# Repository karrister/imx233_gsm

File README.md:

IMX233 GSM
=============

This project started as my thesis project for the University (of applied sciences) of Helsinki. The project is about making a simple open source, Linux based cellular phone. In the heart of the device are an Olimex made Olinuxino (the original) IMX233 development board, connected over an application UART to a SIM900 GPRS GSM-development board. I will also connect a self-made keypad (1 button at first stage) and a self-made screen (1 LED indicator at first stage).

For now I have seized the PCB design for a board combining the two Chips on a shared board, as the final design did not meet the requirements for printing. I will publish the current PCB design files (kicad) here and also plan to continue the work to have a printed board eventually.

Currently I have created a 4.1.1 kernel, running with Debian Jessie on the CPU. The Software for interfacing the Hardware will be a set of Python scripts, communicating with the Chip, parsing the AT commands as well as controlling the custom keypad and screen.

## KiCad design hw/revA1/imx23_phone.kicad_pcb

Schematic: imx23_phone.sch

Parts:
C1, C3: 10uF/6.3V
C2, C4, C5, C6, C7, C8, C9, C10, C12, C24, C29, C31, C33, C34, C46, C48, C49: 100nF
C11, C20, C23, C26, C28, C30, C32, C35, C36, C42, C43, C44, C45, C47, C50, C51, C54, C55: 22uF/6.3V
C13: 470uF
C14, C16, C17, C19, C25: 33pF
C15, C22: 10pF
C18: 4.7uF
C21: NC(10pF)
C27, C39: 1uF
C37, C38: 15pF
C40, C41: NC
C52, C53: 220uF/10V/105C
D1, D5: DIODESCH
D2: BAT54C
D3: LED
D4: AVALANCHE-SMBJ6.0A
J1: AUDIO_3.5
J2, J3: U.FL
J4: MICROSD_SIM_COMBO
J5: USB_MINI
L1: 22uH/1.5A/YS75/7x8mm
L2: FB0805/600R/2A
L3: 470nH/0805/1.76R/250mA
L4: FB0805/600R/200mA
P1: BATT
P2: EXT_GSM_POWER
P3: MIC_P
P4: MIC_N
P5: SPK_P
P6: SPK_GND
P7: RTC_VDD
P8: RTC_GND
P9: GSM_PWR
P10: SPK_N
P11: GSM_DBG_RX
P12: GSM_DBG_TX
P13: STATUS
P14: NETLIGHT
P15: CONN_4
P16: SIM_VPP
P17: LCD_D11
P18: I2C
P19: LCD_CS
P20: 5V_OUT
P21: GPIO4/LRADC0
P22: GPIO2
P23: GPIO3
P24: GPIO1
R1, R12, R14: 120
R2, R3, R23, R26: 1k/1%
R4: NC(0)
R5, R36: 0
R6, R7, R9, R10, R27, R29, R34: 10k
R8: 68
R11: 1k
R13, R15, R24, R43, R44, R45, R46: 4k7
R16: 10
R17, R35, R39, R42: 47k
R18: 0R
R19, R20, R21: 22
R22, R30, R31, R32: 100k
R25, R37, R38: 2k2
R28: 1M
R33: NA(47k)
R40, R41: NC(47k)
SW1: POWER
SW2: REC
T1: PMGD175XN
T2: BSV52
U1: FREESCALE-IMX233
U2: HY5DU121622D
U3: SMA_JACK
U4: SIM900
U5: LCD_NOKIA5110
X1: Q24.000MHz/HC-49SM/SMD/20ppm/20pF

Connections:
+2.5V: C1.1, C2.1, C3.1, C4.1, C5.1, C6.1, C7.1, C8.1, C9.1, C42.1, C44.1, C46.1, C48.1, R2.1, R27.1, U1.38 (VDDIO_EMIQ), U1.45 (VDDIO_EMI1), U1.53 (VDDIO_EMI2), U1.106 (VDDM/LRADC4), U2.1 (VDD1), U2.3 (VDDQ1), U2.9 (VDDQ2), U2.15 (VDDQ3), U2.18 (VDD2), U2.33 (VDD3), U2.55 (VDDQ4), U2.61 (VDDQ5)
+3.3V: C26.1, C28.1, C29.1, C43.1, C45.1, L3.2, P18.1, R24.2, R29.2, R30.2, R31.2, R32.2, R34.1, R35.2, R37.1, R38.1, R43.2, R44.2, R45.2, R46.2, U1.18 (VDDIO33_1), U1.92 (VDDIO33_3), U1.95 (DCDC_VDDIO), U5.6 (VCC)
+5V: C32.1, C34.1, C50.1, C51.1, L2.1, P20.1, U1.102 (VDD5V)
GND: C1.2, C2.2, C3.2, C4.2, C5.2, C6.2, C7.2, C8.2, C10.2, C11.2, C12.2, C13.2, C14.2, C15.2, C16.2, C17.2, C18.2, C19.2, C20.2, C21.2, C22.2, C23.2, C24.2, C25.2, C26.2, C28.2, C29.2, C30.2, C31.2, C32.2, C33.2, C34.2, C35.2, C36.2, C37.2, C38.2, C39.2, C40.2, C41.2, C42.2, C43.2, C44.2, C45.2, C46.2, C47.2, C48.2, C49.2, C50.2, C51.2, C52.2, C53.2, C54.2, C55.2, D4.1 (A), J2.2 (GND), J2.3 (GND), J3.2 (GND), J3.3 (GND), J4.G1 (GND), J4.G2 (GND), J4.G3 (GND), J4.S4 (GND), J4.T6 (VSS), J5.5 (GND), L4.1, P1.2 (PM), P4.1, P6.1, P8.1, P15.3, P18.4, R3.2, R17.2, R22.1, R25.1, R28.2, R33.1, R39.1, R40.1, R41.1, R42.1, T2.2 (E), U1.30 (VSSD1), U1.35 (VSSD2), U1.98 (DCDC_GND), U1.105 (VSSA4), U1.112 (VSSA1), U1.118 (VSSA2), U2.6 (VSSQ1), U2.12 (VSSQ2), U2.34 (VSS1), U2.48 (VSS2), U2.52 (VSSQ3), U2.58 (VSSQ4), U2.64 (VSSQ5), U2.66 (VSS3), U3.2 (GND), U3.3 (GND), U3.4 (GND), U3.5 (GND), U4.17 (GND), U4.18 (GND), U4.20 (MIC_N), U4.29 (GND), U4.39 (GND), U4.45 (GND), U4.46 (GND), U4.53 (GND), U4.54 (GND), U4.58 (GND), U4.59 (GND), U4.61 (GND), U4.62 (GND), U4.63 (GND), U4.64 (GND), U4.65 (GND), U5.8 (GND)
unnamed: R11.2, U4.1 (PWRKEY)
unnamed: P9.1, R11.1, T2.3 (C)
unnamed: R15.2, R17.1, T2.1 (B)
unnamed: R13.2, U4.4 (RI)
unnamed: P14.1, U4.52 (NETLIGHT)
unnamed: P13.1, U4.66 (STATUS)
unnamed: C41.1, J3.1 (SIG), R18.2
unnamed: C40.1, R18.1, U4.60 (RF_ANT)
unnamed: J2.1 (SIG), U3.1 (RF)
unnamed: C18.1, P7.1, U4.26 (VRTC)
unnamed: C35.1, C36.1, D1.2 (K), U1.101 (VDD4P2)
unnamed: R15.1, U1.82 (GPMI_CE0N)
unnamed: R13.1, U1.81 (GPMI_CE1N)
unnamed: J1.2 (L), R14.2, U1.113 (HPL)
unnamed: J1.3 (R), R12.2, U1.109 (HPR)
unnamed: J1.1 (GND), R12.1, R14.1, U1.111 (HP_VGND)
unnamed: P2.1, R4.1
unnamed: J4.T8 (DAT1), R30.1, U1.85 (SSP1_DATA1/I2C_SCL/JTAG_TCLK)
unnamed: J4.S6 (I/O), R21.2
unnamed: P12.1, U4.27 (DEBUG_TXD)
unnamed: P11.1, U4.28 (DEBUG_RXD)
unnamed: J4.S2 (RST), R19.2
unnamed: R20.1, U4.32 (SIM_CLK)
unnamed: J4.S3 (CLK), R20.2
unnamed: R21.1, U4.31 (SIM_DATA)
unnamed: J4.S1 (VCC), U4.30 (SIM_VDD)
unnamed: R35.1, U1.14 (LCD_RS)
unnamed: J4.T1 (DAT2), R32.1, U1.86 (SSP1_DATA2/I2C_SDA/JTAG_RTCK)
unnamed: J4.T7 (DAT0), R31.1, U1.84 (SSP1_DATA0/SPI1_MISO/JTAG_TDI)
unnamed: J4.T3 (CMD), R29.1, U1.83 (SSP1_CMD/SPI1_MOSI/JTAG_TDO)
unnamed: J4.T5 (CLK), U1.90 (SSP1_SCK/SPI1_SCK/JTAG_TRST)
unnamed: J4.T2 (CD/DAT3), R28.1, U1.87 (SSP1_DATA3/SPI1_SS#/JTAG_TMS)
unnamed: R7.2, T1.4 (S2), U4.10 (RXD)
unnamed: R9.2, T1.6 (D1), U1.128 (I2C_SDA/GPMI_CE2N/AUART1_RX)
unnamed: R6.1, T1.1 (S1), U4.9 (TXD)
unnamed: R10.2, T1.3 (D2), U1.127 (I2C_SCL/GPMI_RDY2/AUART1_TX)
unnamed: R6.2, R7.1, T1.2 (G1), T1.5 (G2), U4.15 (VDD_EXT)
unnamed: R19.1, U4.33 (SIM_RST)
unnamed: C27.1, U4.21 (SPK_P)
unnamed: C14.1, P3.1, R8.1
unnamed: C17.1, R8.2, U4.19 (MIC_P)
unnamed: R34.2, SW2.2
unnamed: R36.1, U1.27 (GPMI_D04/LCD_D12/SSP2_DATA4)
unnamed: D2.1 (Anode), U1.125 (PWM0/ROTARYA/DUART_RX)
unnamed: D2.3 (cathode), R24.1
unnamed: D2.2 (AK), P15.1
unnamed: R40.2, R44.1, U1.3 (LCD_D01)
unnamed: R33.2, U1.7 (LCD_D05)
unnamed: C33.1, SW1.2, U1.120 (VDDXTAL)
unnamed: R26.2, U1.119 (PSWITCH)
unnamed: R42.2, R46.1, U1.5 (LCD_D03)
unnamed: R41.2, R45.1, U1.4 (LCD_D02)
unnamed: R39.2, R43.1, U1.2 (LCD_D00)
unnamed: R22.2, R23.1, R26.1, R36.2, SW1.1, SW2.1
unnamed: C49.1, R23.2
unnamed: P22.1, U1.17 (LCD_DOTCK/GPMI_RDY3)
unnamed: J5.S (SHIELD), L4.2
unnamed: P21.1, U1.108 (LRADC0)
unnamed: P23.1, U1.20 (GPMI_ALE/LCD_D17)
unnamed: P24.1, U1.34 (GPMI_WPN)
unnamed: P10.1, U4.22 (SPK_N)
unnamed: P17.1, U1.25 (GPMI_D03/LCD_D11/SSP2_DATA3)
unnamed: R4.2, R5.1, U4.55 (VBAT), U4.56 (VBAT), U4.57 (VBAT)
unnamed: P19.1, U1.32 (GPMI_RDY0/SSP2_DETECT), U5.2 (CS)
unnamed: J4.S5 (VPP), P16.1
unnamed: C22.1, L1.1, U1.99 (DCDC_LP)
unnamed: C38.1, U1.121 (XTALO), X1.1
unnamed: D3.2 (K), R25.2
unnamed: D3.1 (A), U1.88 (SSP1_DETECT/GPMI_CE3N/USB_ID)
unnamed: P15.4, U1.89 (DEBUG)
unnamed: P15.2, U1.126 (PWM1/ROTARYB/DUART_TX)
unnamed: C21.1, L1.2, U1.97 (DCDC_LN1)
unnamed: C39.1, U1.117 (VAG)
unnamed: C20.1, C30.1, C31.1, C47.1, U1.1 (VDDD1), U1.93 (VDDD3), U1.94 (DCDC_VDDD)
unnamed: C23.1, C24.1, U1.96 (DCDC_VDDA), U1.110 (VDDA1)
unnamed: U1.9 (LCD_D07), U5.1 (RST)
unnamed: U1.8 (LCD_D06), U5.3 (DC)
unnamed: U1.91 (PWM2/GPMI_RDY3), U5.7 (LIGHT)
unnamed: U1.33 (GPMI_WRN/SSP2_SCK), U5.5 (CLK)
unnamed: U1.21 (GPMI_RDY1/SSP2_CMD), U5.4 (DIN)
unnamed: J5.3 (D+), U1.124 (USB_DP)
unnamed: D5.1 (A), J5.1 (VBUS)
unnamed: C52.1, C53.1, D4.2 (K), D5.2 (K), L2.2
unnamed: P18.3, R37.2, U1.15 (LCD_HSYNC/I2C_SDA)
unnamed: P18.2, R38.2, U1.11 (LCD_ENABLE/I2C_SCL)
unnamed: J5.2 (D-), U1.123 (USB_DM)
unnamed: C54.1, C55.1, J4.T4 (VDD), L3.1
unnamed: C9.2, C10.1, R2.2, R3.1, U2.49 (VREF)
unnamed: C15.1, C16.1, C19.1, P5.1, R16.1
unnamed: C25.1, C27.2, R16.2
unnamed: U1.72 (EMI_A04), U2.35 (A4)
unnamed: U1.51 (EMI_D08), U2.54 (DQ8)
unnamed: U1.78 (EMI_CKE), U2.44 (CKE)
unnamed: U1.60 (EMI_D14), U2.63 (DQ14)
unnamed: U1.62 (EMI_RASN), U2.23 (/RAS)
unnamed: U1.50 (EMI_D07), U2.13 (DQ7)
unnamed: U1.58 (EMI_D13), U2.62 (DQ13)
unnamed: U1.64 (EMI_A12), U2.42 (A12)
unnamed: U1.73 (EMI_A03), U2.32 (A3)
unnamed: U1.61 (EMI_CASN), U2.22 (/CAS)
unnamed: U1.40 (EMI_DQS1), U2.51 (UDQS)
unnamed: U1.54 (EMI_D10), U2.57 (DQ10)
unnamed: U1.55 (EMI_D11), U2.59 (DQ11)
unnamed: U1.68 (EMI_A08), U2.39 (A8)
unnamed: U1.76 (EMI_A00), U2.29 (A0)
unnamed: U1.69 (EMI_A07), U2.38 (A7)
unnamed: U1.66 (EMI_A10), U2.28 (A10/AP)
unnamed: U1.65 (EMI_A11), U2.41 (A11)
unnamed: U1.56 (EMI_DQM1), U2.47 (UDM)
unnamed: U1.70 (EMI_A06), U2.37 (A6)
unnamed: U1.80 (EMI_BA1), U2.27 (BA1)
unnamed: U1.52 (EMI_D09), U2.56 (DQ9)
unnamed: U1.71 (EMI_A05), U2.36 (A5)
unnamed: U1.59 (EMI_D15), U2.65 (DQ15)
unnamed: U1.74 (EMI_A02), U2.31 (A2)
unnamed: U1.77 (EMI_WEN), U2.21 (/WE)
unnamed: U1.49 (EMI_D06), U2.11 (DQ6)
unnamed: U1.57 (EMI_D12), U2.60 (DQ12)
unnamed: U1.67 (EMI_A09), U2.40 (A9)
unnamed: U1.75 (EMI_A01), U2.30 (A1)
unnamed: U1.46 (EMI_DQM0), U2.20 (LDM)
unnamed: U1.48 (EMI_D05), U2.10 (DQ5)
unnamed: U1.41 (EMI_D00), U2.2 (DQ0)
unnamed: U1.79 (EMI_BA0), U2.26 (BA0)
unnamed: R27.2, U1.63 (EMI_CE0N), U2.24 (/CS)
unnamed: R1.2, U1.37 (EMI_CLKN), U2.46 (/CK)
unnamed: R1.1, U1.36 (EMI_CLK), U2.45 (CK)
unnamed: U1.47 (EMI_D04), U2.8 (DQ4)
unnamed: U1.44 (EMI_D03), U2.7 (DQ3)
unnamed: U1.42 (EMI_D02), U2.5 (DQ2)
unnamed: U1.43 (EMI_D01), U2.4 (DQ1)
unnamed: U1.39 (EMI_DQS0), U2.16 (LDQS)
unnamed: C11.1, C12.1, C13.1, D1.1 (A), P1.1, R5.2, R9.1, R10.1, U1.100 (DCDC_BATTERY), U1.103 (BATT)
unnamed: C37.1, U1.122 (XTALI), X1.2

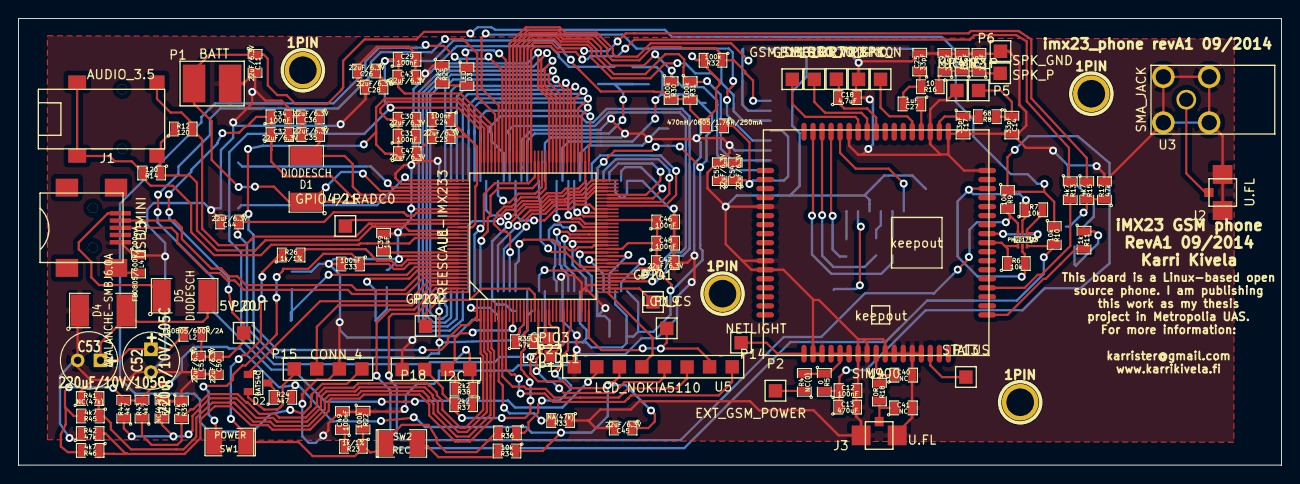
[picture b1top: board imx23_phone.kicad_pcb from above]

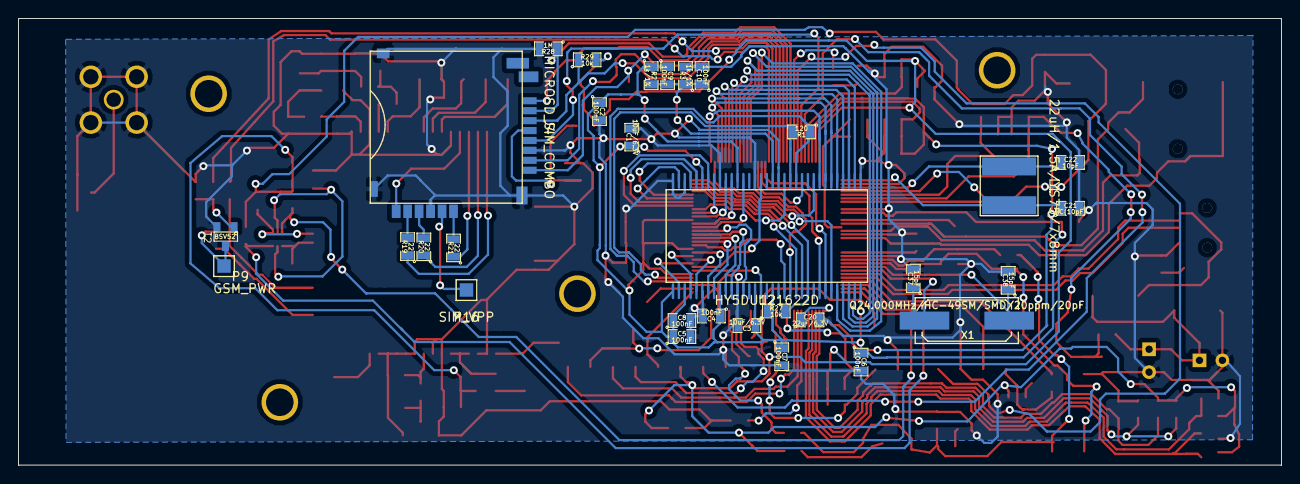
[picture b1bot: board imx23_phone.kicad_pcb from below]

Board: 2 copper layers, 140.0 x 49.5 mm, 153 parts (31 on the bottom side), 138 nets.

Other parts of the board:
1PIN, 1PIN#2, 1PIN#3, 1PIN#4: P***; 1pin

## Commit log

2016-03-19 :circus_tent: Added .gitattributes
2016-03-19 First commit *License and readme files *Basic Python infra stub files
2016-03-19 Infra skeleton *Introducing very basic main infra *Introducing basic classes and functions as stubs
2016-03-19 UART write stub *Bus driver write stub function
2016-08-29 Python framework works *Very basic python framework is now running
2016-09-17 SIM900 connection test *A connection test for SIM900 chip for testing connectivity with the Chip, as well as to the GSM network
2016-09-24 Test supports linux *Now the connection test supports also the serial pointer of linux OS
2016-10-29 Refactoring the main process *Refactoring of the main process, according to the new state machine definition
2016-11-04 Adding logger, action *Adding a class for logging events *Adding a class for actions
2016-11-04 Developed more features *Added some features to modules *Made some integration between modules *Made some changes in the main state machine
2016-11-05 More work. Refactoring tabs *Tabs are now everywhere tabs and not 4 spaces *Made the python script to run again *Work on the screen *Added keypad and screen stubs for accessing HW
2016-11-05 Adding gitignore
2016-11-06 More integration *Fixed reading HW event flow *Fixed reading user event flow *Fixing logger *Misc fixes and integration
2016-11-12 Exception handling *Fixed exception handling (linux) *Modified the priviliges - now able to run python files
2016-11-12 Some HW mocks *Mock for button GPIO *Mock for screen LED
2016-11-12 Extending support for screen update *Now screen update supports action for call dialing
2016-11-14 Fixing debug prints *Fixed some debug prints to not run if no string provided
2017-04-13 Integration with serial port on Linux *Bus driver integration for Linux USB serial port with modem *AT parser integration
2017-04-22 Add filesystem path to HW GPIO *Adding filesystem path for the specific GPIO for LED and switch on GSM board
2017-04-22 Adding version file *Adding a version file to identify script version on the device
2017-05-13 Introducing init bash script *Introducing init bash script that sets up the GPIO and calls the background Python GSM process
2017-05-20 Adding PCB design files
    Adding PCB design files, from 2014.
2017-05-20 Refactoring, adding new message to AT parser *Refactoring some old code. *Adding hang up/no carrier AT response for AT commands parser.
2017-05-20 Version v1.0
2017-05-21 Adding a note for PCB RevA1
2018-01-20 Adding the state of getting disconnected from the call
2018-03-03 Adding state module
    Adding state module for each SW module to know the state of the device
